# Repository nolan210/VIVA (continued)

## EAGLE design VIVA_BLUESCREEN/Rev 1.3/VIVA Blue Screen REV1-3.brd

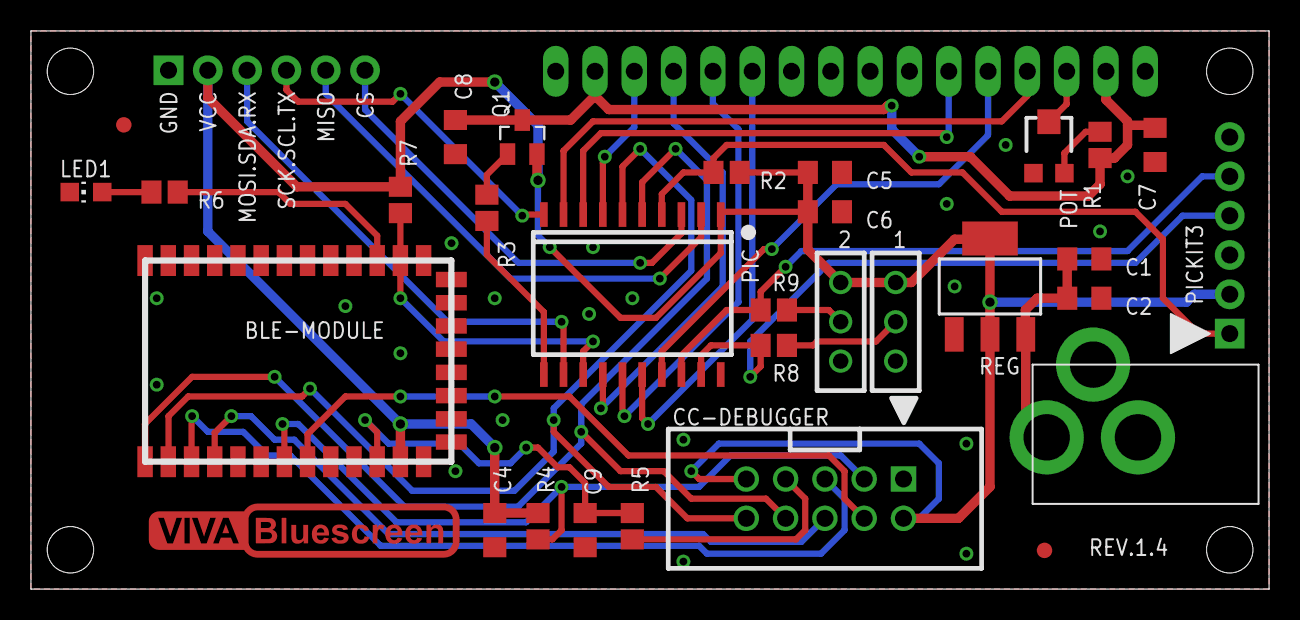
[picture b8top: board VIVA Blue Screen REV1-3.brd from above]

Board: 2 copper layers, 80.0 x 36.1 mm, 31 parts (1 on the bottom side), 35 nets.

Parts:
BLE-MODULE: HM-10; HM-10_EDGE
C1, C4, C5, C8: 4u7; C0805
C2, C6, C9: 47n; C0805
C7: 47u; C0805
CC-DEBUGGER: PINS_TI-CC; PINS_10-2X5
J1: 2.1MMJACKTHM; PJ-102A
J3: PICKIT3; PINS_6_PICKIT3
LED1: CHIP-LED0805
PIC: PIC16F1829; SOP20-NEW
POT: 1k; TC33X
Q1: PNP; SOT23
R1: 4k7; R0805
R2, R4, R7, R8, R9: 10k; R0805
R3, R5, R6: 100; R0805
REG: LM1117; SOT223
SW1, SW2: SWITCH-SPDT
U$1: VIVA_BLUESCREEN_LOGO
U$3: PINS_6SQUARE; PINS_6
X1: HD44780LCD-1602; LCD1602

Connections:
+V: BLE-MODULE.12, C4.2, C5.2, C6.2, CC-DEBUGGER.2, CC-DEBUGGER.9, J3.2, PIC.1, Q1.2, R2.2, R4.2, R7.1, REG.2, REG.4.TAB, SW1.1, SW2.1, U$3.2
BLE.KEY: BLE-MODULE.23, PIC.13, R7.2
BLE.LED: BLE-MODULE.24, R6.2
BLE.RX: BLE-MODULE.2, CC-DEBUGGER.10, PIC.6
BLE.TX: BLE-MODULE.1, CC-DEBUGGER.8, PIC.5
CLK: J3.5, PIC.18, R9.2
DAT: J3.4, PIC.19, R8.2
GND: BLE-MODULE.13, BLE-MODULE.14, BLE-MODULE.21, BLE-MODULE.22, C1.1, C2.1, C4.1, C5.1, C6.1, C7.1, C8.1, C9.1, CC-DEBUGGER.1, J1.RING, J3.3, LED1.C, PIC.20, POT.1, REG.1, SW1.3, SW2.3, U$3.1, X1.1, X1.16
LCD.D4: PIC.16, X1.11
LCD.D5: PIC.15, X1.12
LCD.D6: PIC.14, X1.13
LCD.D7: PIC.7, X1.14
LCD.E: PIC.8, X1.6
LCD.RS: PIC.9, X1.4
LCD.RW: PIC.17, X1.5
LCD_+V: C7.2, C8.2, Q1.3, R1.1, X1.2, X1.15
LCD_CON: PIC.11, R3.1
MCLR: J3.1, PIC.4, R2.1
unnamed: POT.3, R1.2
unnamed: C1.2, C2.2, J1.TIP, REG.3
unnamed: LED1.A, R6.1
unnamed: Q1.1, R3.2
unnamed: BLE-MODULE.8, CC-DEBUGGER.4
unnamed: BLE-MODULE.4, CC-DEBUGGER.6
unnamed: BLE-MODULE.11, C9.2, R5.1
unnamed: R8.1, SW1.2
unnamed: CC-DEBUGGER.7, R5.2
unnamed: BLE-MODULE.3, CC-DEBUGGER.5
unnamed: BLE-MODULE.7, CC-DEBUGGER.3, R4.1
unnamed: R9.1, SW2.2
VIVA.3: PIC.12, U$3.3
VIVA.4: PIC.10, U$3.4
VIVA.5: PIC.2, U$3.5
VIVA.6: PIC.3, U$3.6
VO: POT.2, X1.3

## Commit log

2021-02-27 For educational use only.
2021-02-27 Added VIVA Hardware Repository guide.
2021-02-28 20210227_02
2021-02-28 20210227_03
2021-03-04 3/3/2021 Added Hello_World.txt
2021-03-04 3/3/21 Hello_World.txt
2021-07-15 updated Word document with links to downloads.
2021-07-15 Added Tilt Table, V3
2021-09-07 ATmega328 reference design
2021-10-14 Rev 2
2021-10-22 18650 battery, dcdc converter
2021-10-23 v5 draft
2021-10-23 ATmega PN
